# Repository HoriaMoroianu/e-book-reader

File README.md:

Moroianu Horia-Valentin

# OpenBook

## Diagrama bloc

## Prezentare Generala

Dispozitivul este construit in jurul microcontrolerului **ESP32-C6-WROOM-1-N8**, o componenta performanta ce ofera conectivitate Wi-Fi 6, Bluetooth 5 LE si o arhitectura RISC-V eficienta energetic. Acesta coordoneaza toate componentele periferice prin magistralele **SPI** si **I2C**.

Pentru masurarea timpului, este integrat un modul **RTC DS3231SN**, conectat prin I2C si semnale auxiliare pentru intreruperi si ceas. Pe aceeasi magistrala I2C functioneaza si senzorul **BME688**, responsabil pentru monitorizarea temperaturii, umiditatii, presiunii si compusilor din aer.

Datele pot fi stocate atat pe un **card SD** (SPI), cat si intr-o memorie **Flash NOR de 64MB**, utilizata pentru firmware. Afisajul grafic este realizat printr-un **ePaper Display**, conectat prin SPI, cu pini de control suplimentari pentru functionare eficienta.

Alimentarea este asigurata de un port **USB-C** cu protectie ESD, in combinatie cu un stabilizator **LDO** de 3.3V. Incarcarea bateriei Li-Po este gestionata de un circuit **MCP73831**, iar starea bateriei este monitorizata cu ajutorul unui **MAX17048**, controlat prin I2C.

Dispozitivul include si un conector **Qwiic/Stemma QT**, facilitand extinderea cu senzori compatibili I2C. Butoanele hardware permit controlul direct al functiilor de IO: resetare, boot si control.

## Conectivitate ESP32-C6

| Pin ESP32-C6   | Componenta Asociata                  | Functie                              |
|----------------|--------------------------------------|--------------------------------------|
| IO0            | RTC - DS3231SN                       | INT_RTC (Interrupt)                  |
| IO1            | RTC - DS3231SN                       | Semnal 32KHz                         |
| IO2            | SD Card, ePaper, Flash               | SPI - MISO                           |
| IO3            | ePaper Display                       | EPD BUSY                             |
| IO4            | SD Card                              | SPI - CS                             |
| IO5            | ePaper Display                       | D/C (Data/Command)                   |
| IO6            | SD Card, ePaper, Flash               | SPI - SCK                            |
| IO7            | SD Card, ePaper, Flash               | SPI - MOSI                           |
| IO9            | Buton Boot                           | IO/BOOT                              |
| IO10           | ePaper Display                       | SPI - CS                             |
| IO11           | Flash                                | SPI - Flash CS                       |
| IO12           | USB                                  | USB D−                               |
| IO13           | USB                                  | USB D+                               |
| IO15           | Buton CHANGE                         | IO/CHANGE                            |
| IO16           | Testpad                              | UART TX Debugg                       |
| IO17           | Testpad                              | UART RX Debugg                       |
| IO18           | RTC - DS3231SN                       | RTC Reset                            |
| IO19           | BME688                               | I2C power line                       |
| IO20           | ePaper Display                       | EPD Power supply                     |
| IO21           | RTC, BME688, Qwiic                   | I2C - SDA                            |
| IO22           | RTC, BME688, Qwiic                   | I2C - SCL                            |
| IO23           | ePaper Display                       | Reset                                |
| EN             | Buton Reset                          | IO/RESET                             |
| 3V3            | Toate modulele                       | Alimentare 3.3V                      |
| GND            | Toate modulele                       | Masa                                 |

## BOM

| Componenta            | Sursa                                                                                                                                                                                              | Datasheet                                                                                                                                  | Descriere          |
| ----------------------- | ---------------------------------------------------------------------------------------------------------------------------------------------------------------------------------------------------- | -------------------------------------------------------------------------------------------------------------------------------------------- | -------------------- |
| XC6220A331MR-G        | [Product Page](https://ro.mouser.com/ProductDetail/Torex-Semiconductor/XC6220A331MR-G?qs=AsjdqWjXhJ8ZSWznL1J0gg%3D%3D)                                                                             | [Datasheet](https://eu.mouser.com/datasheet/2/760/xc6220-3371556.pdf)                                                                      | LDO regulator      |
| W25Q512JVEIQ          | [Product Page](https://ro.mouser.com/ProductDetail/Winbond/W25Q512JVEIQ?qs=l7cgNqFNU1jw6svr3at6tA%3D%3D)                                                                                           | [Datasheet](https://ro.mouser.com/datasheet/2/949/Winbond_W25Q512JV_Datasheet-3240039.pdf)                                                 | Nor flash          |
| USBLC6-2SC6Y          | [Product Page](https://ro.mouser.com/ProductDetail/STMicroelectronics/USBLC6-2SC6Y?qs=gNDSiZmRJS%2FOgDexvXkdow%3D%3D)                                                                              | [Datasheet](https://ro.mouser.com/datasheet/2/389/usblc6_2sc6y-1852505.pdf)                                                                | USB ESD prot       |
| SI1308EDL-T1-GE3      | [Product Page](https://ro.mouser.com/ProductDetail/Vishay-Semiconductors/SI1308EDL-T1-GE3?qs=bX1%252BNvsK%2FBramh9tgpOaEw%3D%3D)                                                                   | [Datasheet](https://www.vishay.com/docs/63399/si1308edl.pdf)                                                                               | MOSFET             |
| USB4110-GF-A          | [Product Page](https://ro.mouser.com/ProductDetail/GCT/USB4110-GF-A?qs=KUoIvG%2F9IlYiZvIXQjyJeA%3D%3D)                                                                                             | [Datasheet](https://ro.mouser.com/datasheet/2/837/GCT_USB4110_Product_Drawing___20k_cycles-3455479.pdf)                                    | USB C              |
| PRT-14417             | [Product Page](https://ro.mouser.com/ProductDetail/SparkFun/PRT-14417?qs=wd5RIQLrsJhgdz%2FpmZ%2F3GQ%3D%3D)                                                                                         | [Datasheet](https://ro.mouser.com/datasheet/2/813/Qwiic_Connector_Datasheet-1223982.pdf)                                                   | Qwiic              |
| PGB1010603MR          | [Product Page](https://ro.mouser.com/ProductDetail/Littelfuse/PGB1010603MR?qs=gu7KAQ731URLg4GSnNNN7Q%3D%3D)                                                                                        | [Datasheet](https://www.littelfuse.com/assetdocs/pulseguard-esd-suppressors-pgb1-datasheet?assetguid=8a337998-d54d-466b-be4e-dc5bcd1f9321) | ESD prot diode     |
| MBR0530-TP            | [Product Page](https://ro.mouser.com/ProductDetail/Micro-Commercial-Components-MCC/MBR0530-TP?qs=KFo7JewZbUECRHkxGanrdg%3D%3D)                                                                     | [Datasheet](https://ro.mouser.com/datasheet/2/258/MBR0520_MBR0580_SOD123_-2492194.pdf)                                                     | Schottky diode     |
| MAX17048G+T10         | [Product Page](https://ro.mouser.com/ProductDetail/Analog-Devices-Maxim-Integrated/MAX17048G%2bT10?qs=D7PJwyCwLAoGnnn8jEPRBQ%3D%3D)                                                                | [Datasheet](https://ro.mouser.com/datasheet/2/609/MAX17048_MAX17049-3469099.pdf)                                                           | Battery Management |
| FH34SRJ-24S-0.5SH(99) | [Product Page](https://ro.mouser.com/ProductDetail/Hirose-Connector/FH34SRJ-24S-0.5SH99?qs=vcbW%252B4%252BSTIpKBl5ap9J8Fw%3D%3D)                                                                   | [Datasheet](https://ro.mouser.com/datasheet/2/185/FH34SRJ_24S_0_5SH_99__CL0580_1255_6_99_2DDrawing_0-1615044.pdf)                          | EPD connector      |
| MCP73831-2ACI/MC      | [Product Page](https://ro.mouser.com/ProductDetail/Microchip-Technology/MCP73831-2ACI-MC?qs=hH%252BOa0VZEiBneYTVdpuVdg%3D%3D)                                                                      | [Datasheet](https://ro.mouser.com/datasheet/2/268/MCP73831_Family_Data_Sheet_DS20001984H-3441711.pdf)                                      | Battery controller |
| BME688                | [Product Page](https://ro.mouser.com/ProductDetail/Bosch-Sensortec/BME688?qs=IS%252B4QmGtzzqQoVDscqwx3A%3D%3D)                                                                                       | [Datasheet](https://ro.mouser.com/datasheet/2/783/bst_bme688_fl000-2307034.pdf)                                                            | Sensor             |
| SD0805S020S1R0        | [Product Page](https://ro.mouser.com/ProductDetail/KYOCERA-AVX/SD0805S020S1R0?qs=jCA%252BPfw4LHbpkAoSnwrdjw%3D%3D)                                                                                 | [Datasheet](https://ro.mouser.com/datasheet/2/40/schottky-3165252.pdf)                                                                     | Schottky diode     |
| B72540T0300K062       | [Product Page](https://ro.mouser.com/ProductDetail/EPCOS-TDK/B72540T0300K062?qs=dEfas%2FXlABK4d0Dv0OnYYg%3D%3D)                                                                                    | [Datasheet](https://www.tdk-electronics.tdk.com/inf/75/db/CTVS_14/Surge_protection_series.pdf)                                             | Varistor           |
| ESP32-C6-WROOM-1-N8   | [Product Page](https://ro.mouser.com/ProductDetail/Espressif-Systems/ESP32-C6-WROOM-1-N8?qs=8Wlm6%252BaMh8ST02Gmwp74cw%3D%3D)                                                                      | [Datasheet](https://ro.mouser.com/datasheet/2/891/Espressif_ESP32_C6_WROOM_1__Datasheet_V0_1_PRELIMI-3239987.pdf)                          | ESP32              |
| DS3231SN#             | [Product Page](https://ro.mouser.com/ProductDetail/Analog-Devices-Maxim-Integrated/DS3231SN?qs=1eQvB6Dk1vhUlr8%2FOrV0Fw%3D%3D)                                                                     | [Datasheet](https://ro.mouser.com/datasheet/2/609/DS3231-3421123.pdf)                                                                      | RTC                |
| CPH3225A              | [Product Page](https://ro.mouser.com/ProductDetail/Seiko-Semiconductors/CPH3225A?qs=3etwrb1wR%252BhUOph6lAO7eg%3D%3D)                                                                              | [Datasheet](https://ro.mouser.com/datasheet/2/360/Seiko_Instruments_MicroBattery_E_20230330_2024Jan_-3561061.pdf)                          | Supercap           |
| EVQ-P4MB3K            | [Product Page](https://ro.mouser.com/ProductDetail/Panasonic/EVQ-P4MB3K?qs=0aNVN3t2tDvlcmyoDZjvlA%3D%3D)                                                                                           | [Datasheet](https://4donline.ihs.com/images/VipMasterIC/IC/PANA/PANA-S-A0000771493/PANA-S-A0000771493-1.pdf)                               | Buttons            |
| BD5229G-TR            | [Product Page](https://ro.mouser.com/ProductDetail/ROHM-Semiconductor/BD5229G-TR?qs=4kLU8WoGk0vvnhrrYwdszw%3D%3D)                                                                                  | [Datasheet](https://fscdn.rohm.com/en/products/databook/datasheet/ic/power/voltage_detector/bd52xxg-e.pdf)                                 | Voltage detector   |
| 744043680             | [Product Page](https://ro.mouser.com/ProductDetail/Wurth-Elektronik/744043680?qs=PGXP4M47uW6VkZq%252BkzjrHA%3D%3D)                                                                                 | [Datasheet](https://www.we-online.com/components/products/datasheet/744043680.pdf)                                                         | Inductor           |
| R0402                 | [Product Page](https://ro.mouser.com/c/passive-components/resistors/smd-resistors-chip-resistors/?case%20code%20-%20in=0402)                                                                       | [Datasheet](https://www.vishay.com/docs/28700/mcx0x0xpre.pdf)                                                                              | Resistor 0402      |
| DMG2305UX-7           | [Product Page](https://ro.mouser.com/ProductDetail/Diodes-Incorporated/DMG2305UX-7?qs=L1DZKBg7t5F%2FNBHrjfxC%252Bg%3D%3D)                                                                          | [Datasheet](https://www.diodes.com/assets/Datasheets/DMG2305UX.pdf)                                                                        | MOSFET             |
| 112A-TAAR-R03         | [Product Page](https://store.comet.srl.ro/Catalogue/Product/43497/?mark=2)                                                                                                                         | [Datasheet](https://www.attend.com.tw/data/download/file/112A-TAAR-R03_Spec.pdf)                                                           | SD Socket          |
| T491B107M006AT        | [Product Page](https://ro.mouser.com/ProductDetail/KEMET/T491B107M006AT?qs=U312oeP%2FpiHOgyk6KO2m0g%3D%3D)                                                                                         | [Datasheet](https://ro.mouser.com/datasheet/2/447/KEM_T2005_T491-3316937.pdf)                                                              | Tantalum Capacitor |
| LSM0603472V           | [Product Page](https://ro.mouser.com/ProductDetail/VCC/LSM0603472V?qs=%252BEew9%252B0nqrBygsW37Z2ISQ%3D%3D)                                                                                        | [Datasheet](https://ro.mouser.com/datasheet/2/423/LSM0603472V_(1)-1379786.pdf)                                                             | LED                |
| C0402C475K8PACTU      | [Product Page](https://ro.mouser.com/c/passive-components/capacitors/ceramic-capacitors/mlccs-multilayer-ceramic-capacitors/multilayer-ceramic-capacitors-mlcc-smd-smt/?case%20code%20-%20in=0402) | [Datasheet](https://ro.mouser.com/datasheet/2/447/KEM_C1006_X5R_SMD-3316465.pdf)                                                           | Capacitor 0402     |

## Imagini

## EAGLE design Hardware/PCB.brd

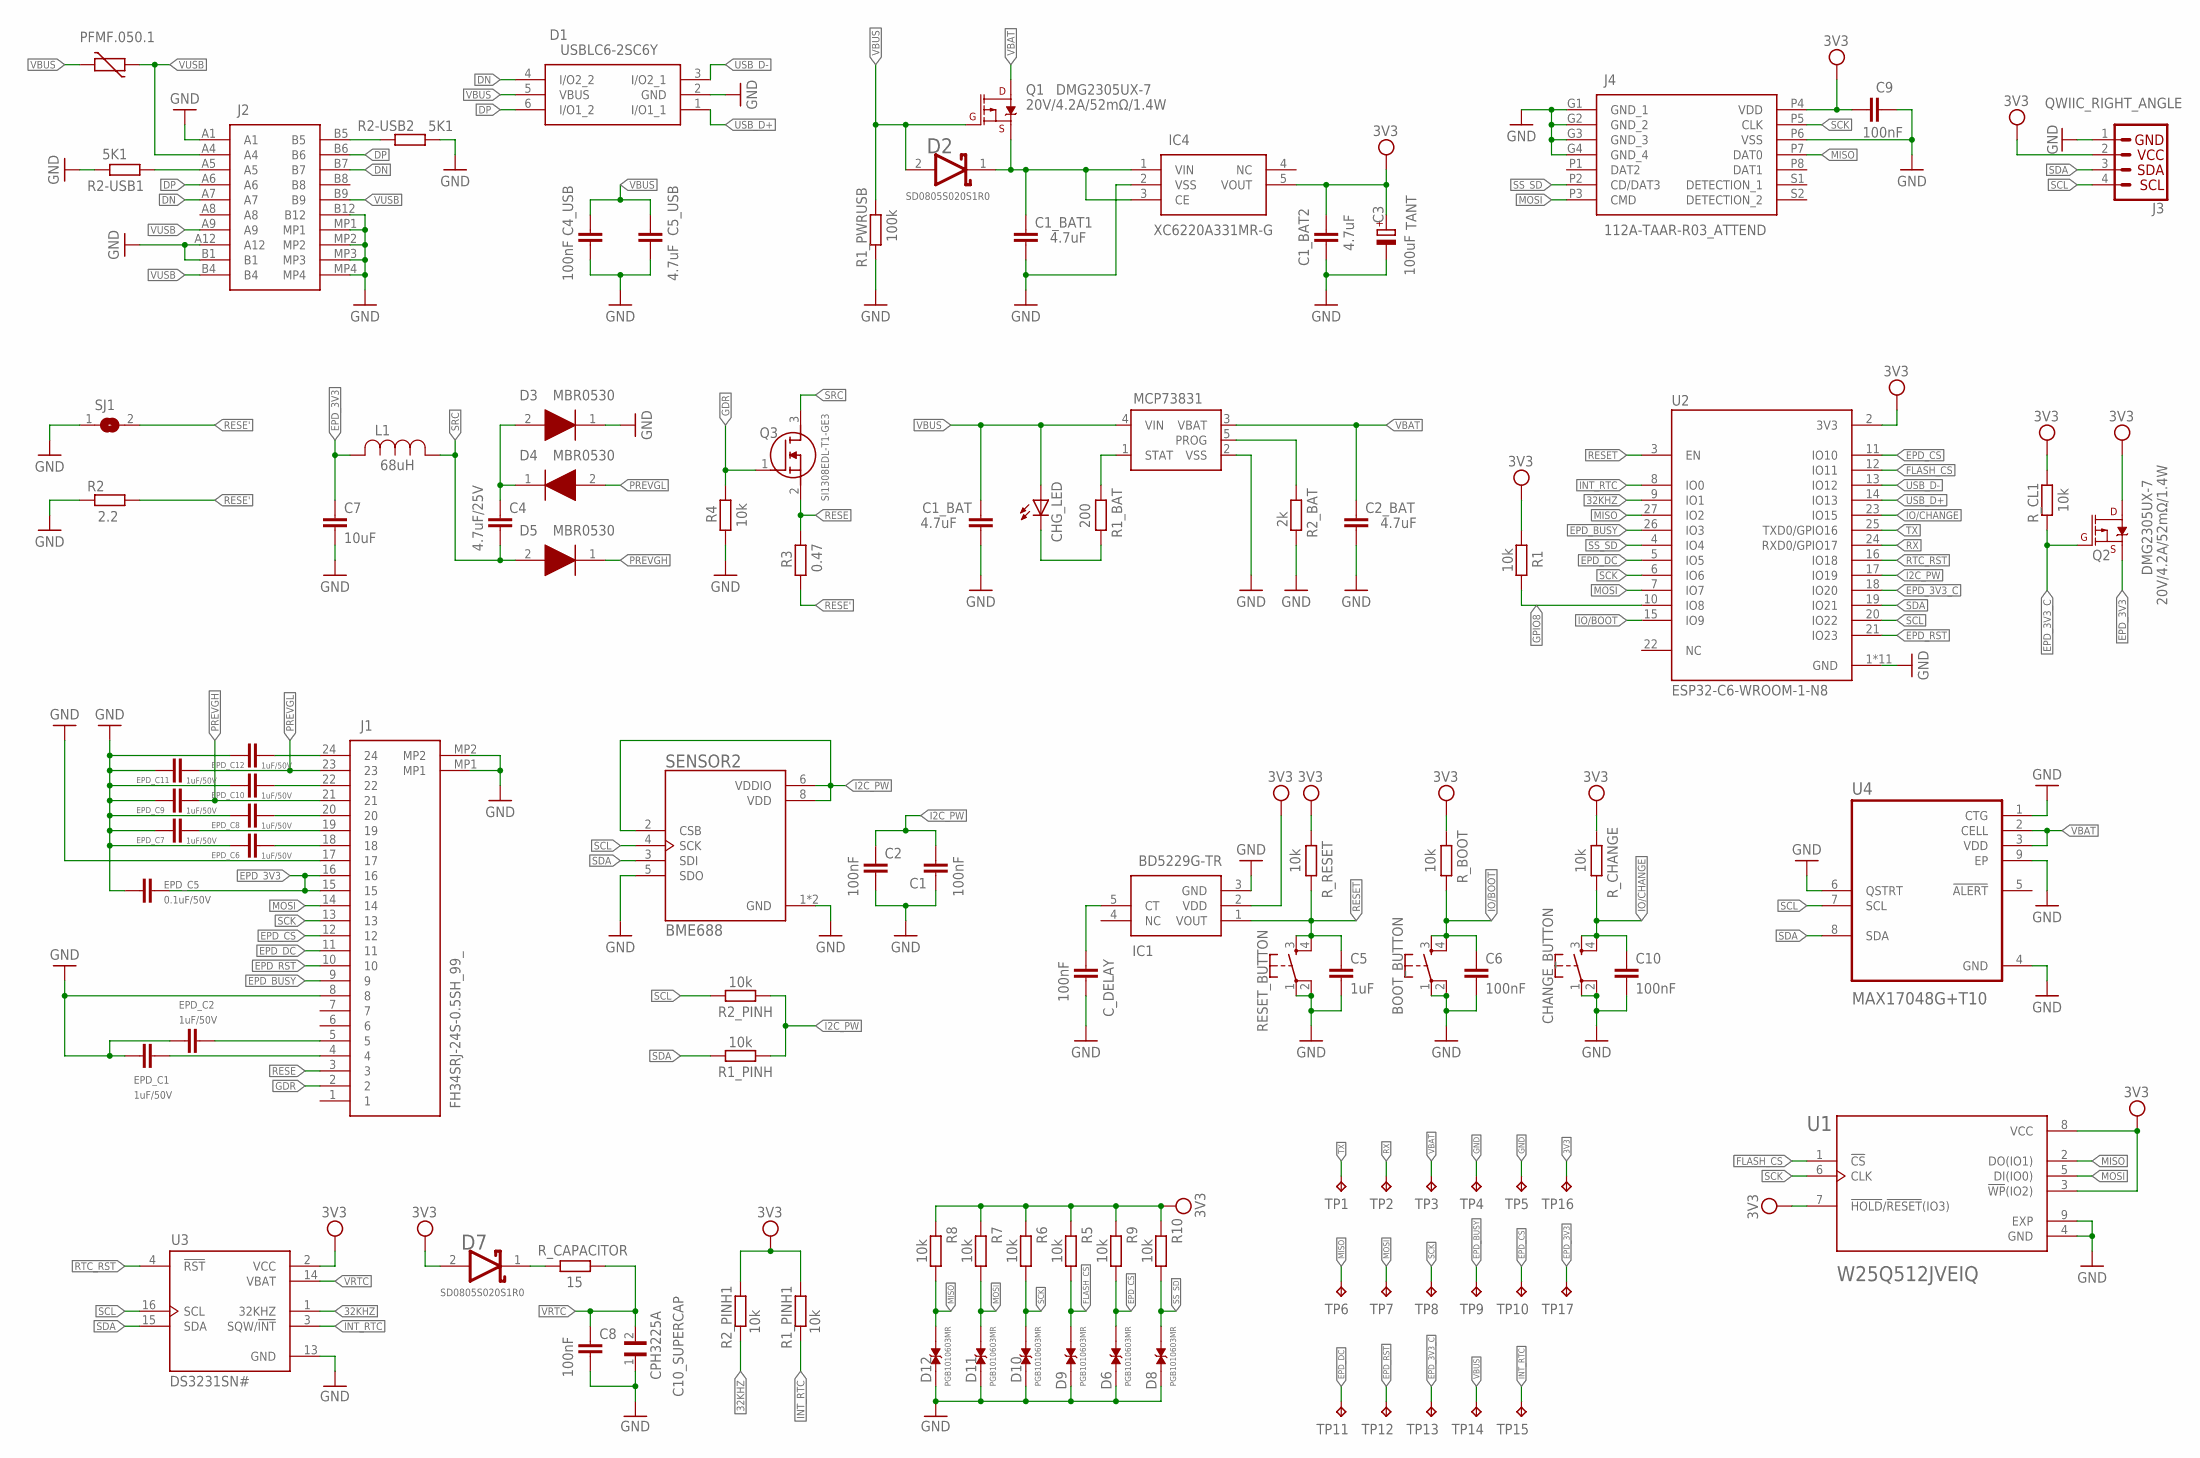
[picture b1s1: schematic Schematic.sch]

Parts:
BOOT_BUTTON: BUTTON_CUSYOMV1; MYBUTTON
C1, C2, C4_USB, C6, C8, C9, C10: 100nF; EAGLE-LTSPICE_C0402
C1_BAT, C1_BAT1, C1_BAT2, C2_BAT, C5_USB: 4.7uF; EAGLE-LTSPICE_C0402
C3: 100uF; RCL_CT3528
C4: 4.7uF/25V; EAGLE-LTSPICE_C0402
C5: 1uF; EAGLE-LTSPICE_C0402
C7: 10uF; EAGLE-LTSPICE_C0402
C10_SUPERCAP: CPH3225A; CAPCP3225X100N
CHANGE_BUTTON: BUTTON_CUSYOMV1; MYBUTTON
CHG_LED: ADAFRUIT_LEDCHIP-LED0603; ADAFRUIT_CHIP-LED0603
C_DELAY: 100nF; EAGLE-LTSPICE_C0402
D1: USBLC6-2SC6Y; SOT95P280X145-6N
D2, D7: ESP32_WROVER_AVX---SD0805S020S1R0_AVX_SD0805S020S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; ESP32_WROVER_AVX---SD0805S020S1R0_AVX_SD0805S020S1R0_0
D3, D4, D5: MBR0530; SOD3716X135N
D6, D8, D9, D10, D11, D12: PGB1010603MR; DIOC1608X36N
EPD_C1, EPD_C2, EPD_C6, EPD_C7, EPD_C8, EPD_C9, EPD_C10, EPD_C11, EPD_C12: 1uF/50V; EAGLE-LTSPICE_C0402
EPD_C5: 0.1uF/50V; EAGLE-LTSPICE_C0402
IC1: BD5229G-TR; SOT95P280X125-5N
IC4: XC6220A331MR-G; SOT95P280X120-5N
J1: FH34SRJ-24S-0.5SH_99_; FH34SRJ24S05SH99
J2: SAMACSYS_PARTS_USB4110-GF-A; SAMACSYS_PARTS_USB4110GFA
J3: QWIIC_RIGHT_ANGLE; JST04_1MM_RA
J4: 112A-TAAR-R03_ATTEND; 112ATAARR03ATTEND
L1: 744043680IND_4828-WE-TPC_WRE; IND_4828-WE-TPC_WRE
PFMF.050.1: ESP32C6_VARISTORCN1812; ESP32C6_VARISTOR_CT/CN1812
Q1, Q2: 20V/4.2A/52mΩ/1.4W; ESP32_WROVER_SPARKFUN-DISCRETESEMI_SOT23-3
Q3: SI1308EDL-T1-GE3; SOT65P210X110-3N
R1, R1_PINH, R1_PINH1, R2_PINH, R2_PINH1, R4, R5, R6, R7, R8, R9, R10: 10k; ESP32_WROVER_EAGLE-LTSPICE_R0402
R1_BAT: 200; ESP32_WROVER_EAGLE-LTSPICE_R0402
R1_PWRUSB: 100k; ESP32_WROVER_EAGLE-LTSPICE_R0402
R2: 2.2; ESP32_WROVER_EAGLE-LTSPICE_R0402
R2-USB1, R2-USB2: 5K1; ESP32_WROVER_EAGLE-LTSPICE_R0402
R2_BAT: 2k; ESP32_WROVER_EAGLE-LTSPICE_R0402
R3: 0.47; ESP32_WROVER_EAGLE-LTSPICE_R0402
RESET_BUTTON: BUTTON_CUSYOMV1; MYBUTTON
R_BOOT: 10k; ESP32_WROVER_EAGLE-LTSPICE_R0402
R_CAPACITOR: 15; ESP32_WROVER_EAGLE-LTSPICE_R0402
R_CHANGE: 10k; ESP32_WROVER_EAGLE-LTSPICE_R0402
R_CL1: 10k; ESP32_WROVER_EAGLE-LTSPICE_R0402
R_RESET: 10k; ESP32_WROVER_EAGLE-LTSPICE_R0402
SENSOR2: ESP32_WROVER_BME680_BME680; ESP32_WROVER_BME680_PSON80P300X300X100-8N
SJ1: SJ
TP1, TP2, TP3, TP4, TP5, TP6, TP7, TP8, TP9, TP10, TP11, TP12, TP13, TP14, TP15, TP16, TP17: TPTP20R; TP20R
U1: W25Q512JVEIQ; SON127P600X800X80-9N
U2: ESP32-C6-WROOM-1-N8; XCVR_ESP32-C6-WROOM-1-N8
U3: DS3231SN#; SOIC127P1032X265-16N
U4: MAX17048G+T10; SON50P200X200X80-9N
U5: ESP32_WROVER_SPARKFUN-IC-POWER_MCP73831; ESP32_WROVER_SPARKFUN-IC-POWER_SOT23-5

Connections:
3V3: C1_BAT2.1, C3.+, C9.1, D7.2 (ANODE), IC1.2 (VDD), IC4.5 (VOUT), J3.2, J4.P4 (VDD), Q2.3 (D), R1.2, R1_PINH1.2, R2_PINH1.2, R5.2, R6.2, R7.2, R8.2, R9.2, R10.2, R_BOOT.1, R_CHANGE.1, R_CL1.2, R_RESET.1, TP16.TP, U1.3 (!WP!(IO2)), U1.7 (!HOLD!/!RESET!(IO3)), U1.8 (VCC), U2.2 (3V3), U3.2 (VCC)
32KHZ: R2_PINH1.1, U2.9 (IO1), U3.1 (32KHZ)
DN: D1.4 (I/O2_2), J2.A7, J2.B7
DP: D1.6 (I/O1_2), J2.A6, J2.B6
EPD_3V3: C7.1, EPD_C5.1, J1.15, J1.16, L1.2, Q2.2 (S), TP17.TP
EPD_3V3_C: Q2.1 (G), R_CL1.1, TP13.TP, U2.18 (IO20)
EPD_BUSY: J1.9, TP9.TP, U2.26 (IO3)
EPD_CS: D6.2, J1.12, R9.1, TP10.TP, U2.11 (IO10)
EPD_DC: J1.11, TP11.TP, U2.5 (IO5)
EPD_RST: J1.10, TP12.TP, U2.21 (IO23)
FLASH_CS: D9.2, R5.1, U1.1 (!CS), U2.12 (IO11)
GDR: J1.2, Q3.1 (G), R4.2
GND: BOOT_BUTTON.1, BOOT_BUTTON.2, C1.2, C1_BAT.2, C1_BAT1.2, C1_BAT2.2, C2.2, C2_BAT.2, C3.-, C4_USB.2, C5.2, C5_USB.2, C6.2, C7.2, C8.2, C9.2, C10.2, C10_SUPERCAP.1, CHANGE_BUTTON.1, CHANGE_BUTTON.2, C_DELAY.2, D1.2 (GND), D3.1 (K), D6.1, D8.1, D9.1, D10.1, D11.1, D12.1, EPD_C1.2, EPD_C2.2, EPD_C5.2, EPD_C6.2, EPD_C7.2, EPD_C8.2, EPD_C9.2, EPD_C10.2, EPD_C11.2, EPD_C12.2, IC1.3 (GND), IC4.2 (VSS), J1.8, J1.17, J1.MP1, J1.MP2, J2.A1, J2.A12, J2.B1, J2.B12, J2.MP1, J2.MP2, J2.MP3, J2.MP4, J3.1, J4.G1 (GND_1), J4.G2 (GND_2), J4.G3 (GND_3), J4.G4 (GND_4), J4.P6 (VSS), R1_PWRUSB.1, R2.1, R2-USB1.1, R2-USB2.2, R2_BAT.1, R4.1, RESET_BUTTON.1, RESET_BUTTON.2, SENSOR2.1 (GND), SENSOR2.5 (SDO), SENSOR2.7 (GND), SJ1.1, TP4.TP, TP5.TP, U1.4 (GND), U1.9 (EXP), U2.1 (GND), U2.28 (GND), U2.29_1 (GND), U2.29_2 (GND), U2.29_3 (GND), U2.29_4 (GND), U2.29_5 (GND), U2.29_6 (GND), U2.29_7 (GND), U2.29_8 (GND), U2.29_9 (GND), U3.13 (GND), U4.1 (CTG), U4.4 (GND), U4.6 (QSTRT), U4.9 (EP), U5.2 (VSS)
GPIO8: R1.1, U2.10 (IO8)
I2C_PW: C1.1, C2.1, R1_PINH.2, R2_PINH.2, SENSOR2.2 (CSB), SENSOR2.6 (VDDIO), SENSOR2.8 (VDD), U2.17 (IO19)
INT_RTC: R1_PINH1.1, TP15.TP, U2.8 (IO0), U3.3 (SQW/!INT)
IO/BOOT: BOOT_BUTTON.3, BOOT_BUTTON.4, C6.1, R_BOOT.2, U2.15 (IO9)
IO/CHANGE: C10.1, CHANGE_BUTTON.3, CHANGE_BUTTON.4, R_CHANGE.2, U2.23 (IO15)
MISO: D12.2, J4.P7 (DAT0), R8.1, TP6.TP, U1.2 (DO(IO1)), U2.27 (IO2)
MOSI: D11.2, J1.14, J4.P3 (CMD), R7.1, TP7.TP, U1.5 (DI(IO0)), U2.7 (IO7)
unnamed: D7.1 (CATHODE), R_CAPACITOR.2
unnamed: J2.A5, R2-USB1.2
unnamed: J2.B5, R2-USB2.1
unnamed: C1_BAT1.1, D2.1 (CATHODE), IC4.1 (VIN), IC4.3 (CE), Q1.2 (S)
unnamed: C4.1, D3.2 (A), D4.1 (K)
unnamed: R2_BAT.2, U5.5 (PROG)
unnamed: EPD_C12.1, J1.24
unnamed: R1_BAT.1, U5.1 (STAT)
unnamed: CHG_LED.C, R1_BAT.2
unnamed: C_DELAY.1, IC1.5 (CT)
unnamed: EPD_C1.1, J1.4
unnamed: EPD_C2.1, J1.5
unnamed: EPD_C6.1, J1.18
unnamed: EPD_C7.1, J1.19
unnamed: EPD_C8.1, J1.20
unnamed: EPD_C10.1, J1.22
PREVGH: D5.1 (K), EPD_C9.1, J1.21
PREVGL: D4.2 (A), EPD_C11.1, J1.23
RESE: J1.3, Q3.2 (S), R3.2
RESE': R2.2, R3.1, SJ1.2
RESET: C5.1, IC1.1 (VOUT), RESET_BUTTON.3, RESET_BUTTON.4, R_RESET.2, U2.3 (EN)
RTC_RST: U2.16 (IO18), U3.4 (!RST)
RX: TP2.TP, U2.24 (RXD0/GPIO17)
SCK: D10.2, J1.13, J4.P5 (CLK), R6.1, TP8.TP, U1.6 (CLK), U2.6 (IO6)
SCL: J3.4, R2_PINH.1, SENSOR2.4 (SCK), U2.20 (IO22), U3.16 (SCL), U4.7 (SCL)
SDA: J3.3, R1_PINH.1, SENSOR2.3 (SDI), U2.19 (IO21), U3.15 (SDA), U4.8 (SDA)
SRC: C4.2, D5.2 (A), L1.1, Q3.3 (D)
SS_SD: D8.2, J4.P2 (CD/DAT3), R10.1, U2.4 (IO4)
TX: TP1.TP, U2.25 (TXD0/GPIO16)
USB_D+: D1.1 (I/O1_1), U2.14 (IO13)
USB_D-: D1.3 (I/O2_1), U2.13 (IO12)
VBAT: C2_BAT.1, Q1.3 (D), TP3.TP, U4.2 (CELL), U4.3 (VDD), U5.3 (VBAT)
VBUS: C1_BAT.1, C4_USB.1, C5_USB.1, CHG_LED.A, D1.5 (VBUS), D2.2 (ANODE), PFMF.050.1.2, Q1.1 (G), R1_PWRUSB.2, TP14.TP, U5.4 (VIN)
VRTC: C8.1, C10_SUPERCAP.2, R_CAPACITOR.1, U3.14 (VBAT)
VUSB: J2.A4, J2.A9, J2.B4, J2.B9, PFMF.050.1.1

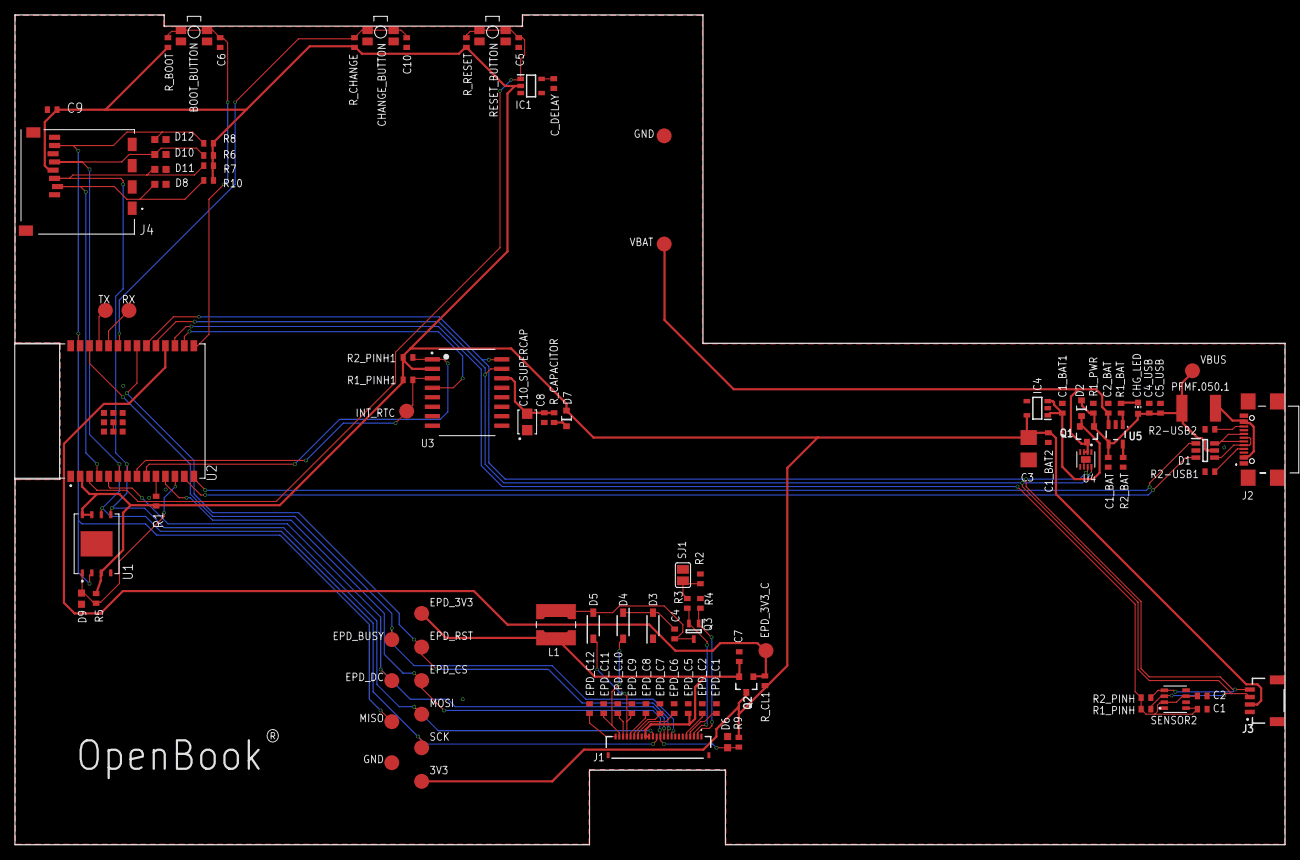
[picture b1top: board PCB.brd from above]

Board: 2 copper layers, 170.2 x 111.2 mm, 103 parts (0 on the bottom side), 55 nets.

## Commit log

2025-04-06 Added project files
2025-04-16 Update PCB design with Via Stitching + board dimension
2025-04-16 Update documentation with hardware description + images

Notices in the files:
parts and their libraries:
COPYRIGHT: Copyright (C) 2024 Ultra Librarian. All rights reserved.
